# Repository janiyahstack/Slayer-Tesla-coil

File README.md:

# Slayer-Tesla-coil
A slayer Excited Tesla coil is a low power solid state tesla coil. A tesla coil is a high frequency transformer that is used to generate high voltages of electricity. It is self-oscillating and does not require precise tuning. A tesla coil was first created by Nikola Tesla in 1891, at the time it was a transformative step in his dream of acquiring wireless transmission of electricity, while we continue to use wire to transmit energy till date, it makes for an exciting project.
I was most inspired to make a Tesla coil by one of my fellow hack clubbers (whose name i cant remember), who made me realize that a tesla coil was quite achievable to make and design. i have been interested in it for a while and it was fun to do.
I built this by first understanding the physics behind a Tesla coil; electromagnetic induction. Then i made a schematic, i read more which led to consequential iterations of the schematic. I did the footprints assignments using Mouser Electronics and eventually updated my footprint library. i concluded by making the PCB(some of the parts are external tho) and viola!!

STEP 1
I did research on Tesla coils. Theres a lot of info about spark gap tesla coils but i decided to go with a slayer excited tesla coil instead utilizing either a feedback coil or a transistor. More details canbe found in the journal.md. Anyways after deciding on this. I read a bunch of instructions and watched YouTube videos and then made the schematic.

STEP 2
I got carried away although doing the footprints assignment but i do think it helped a lot in making the BOM and i made a PCB cause i thought it will be useful which it could be but my tesla coil is not using a PCB

step 3
I made the CAD which also helped me narrow down the specifications etcetra, get a better idea of what i am trying to do and gave me resources to use o calculate the resonant frequency which is important but not too much in a slayer excited tesla coil

step 4
I made the BOM, i looked through Ali Express for stuff, i decided on a battery which i hope i did well cause i dont want to use an adapter and voila. More details in Journal.md

The BOM
pandoc -f csv Sheet1.csv -o output.md

https://docs.google.com/spreadsheets/d/1osx8s_dKkFnwftt5uLbFzMi76YqxEO74YxG5Nzp4THI/edit?usp=sharing

The Schematic

The CAD

| Reference | QTY | Component | Value | Notes | Estimated Prices | Link |
|---|---:|---|---|---|---:|---|
| Q2 | 1 | NPN Power Transistor | TIP31C | TO-220 Package | $1.10 per 10pcs | https://a.aliexpress.com/_EGoSctg |
| R2 | 1 | Resistor | 1kohms | Axial | Available | Available |
| C1 | 1 | Ceramic Capacitor | 100nF, 50V | Radial | $1.10 per 10pcs | https://a.aliexpress.com/_ExHqb2e |
| D2 | 1 | Diode | BAV16W | Fast switching | $0.86 for 20pcs | https://a.aliexpress.com/_EG9ENKm |
| L1 | 1 | Primary coil | 4 turns, 0.8mm magnet wire | Custom wound | $2.80 | https://a.aliexpress.com/_EzIT5KI |
| L2 | 1 | Secondary coil | 25 turns, 0.2mm magnet wire | Custom wound | $1.10 | https://a.aliexpress.com/_EIRpH5y |
| L3 | 1 | Feedback coil | 3 turns, 0.6mm magnet wire | Custom wound | $1.10 | https://a.aliexpress.com/_EIRpH5y |
| BT1 | 1 | Power supply | 9V Lithium ion battery | | $1.10 | https://a.aliexpress.com/_EwdnAp0 |
| 2 pin screw terminal | 2 | 2-pin screw terminal | 2-pin screw terminal | Power input | $1.23 | https://a.aliexpress.com/_Eze3ZSI |
| Perf Board | 1 | Perfboard | 7×9cm protoboard | Circuit Assembly | $1.10 | https://a.aliexpress.com/_EyrP0P4 |
| Solder iron | 1 | Solder Iron | USB or mains powered | Required tool | $6.96 | https://a.aliexpress.com/_EwgpuvC |
| PVC pipe | 1 | PVC pipe | 4 inches | Coil former | $1.10 for 2 pcs | https://a.aliexpress.com/_EzJuh94 |
| | | | | **Total** | **$19.55** | |

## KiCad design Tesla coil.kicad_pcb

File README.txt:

# Slayer-Tesla-coil
A slayer Excited Tesla coil is a low power solid state tesla coil. A tesla coil is a high frequency transformer that is used to generate high voltages of electricity. It is self-oscillating and does not require precise tuning. A tesla coil was first created by Nikola Tesla in 1891, at the time it was a transformative step in his dream of acquiring wireless transmission of electricity, while we continue to use wire to transmit energy till date, it makes for an exciting project.
I was most inspired to make a Tesla coil by one of my fellow hack clubbers (whose name i cant remember), who made me realize that a tesla coil was quite achievable to make and design. i have been interested in it for a while and it was fun to do.
I built this by first understanding the physics behind a Tesla coil; electromagnetic induction. Then i made a schematic , i read more which led to consequential iterations of the schematic. I did the footprints assignments using Mouser Electronics and eventually updated my footprint library. i concluded by making the PCB(some of the parts are external tho) and viola!!
.png)
.png).

STEP 1
I did research on Tesla coils. Theres a lot of info about spark gap tesla coils but i decided to go with a slayer excited tesla coil instead utilizing either a feedback coil or a transistor. More details canbe found in the journal.md

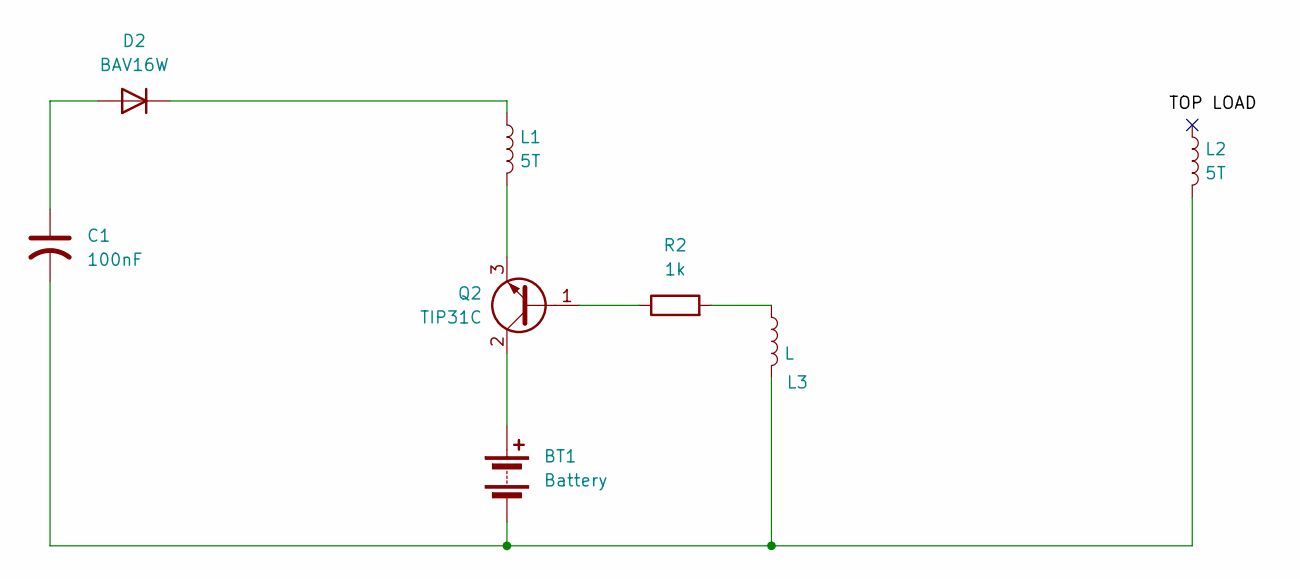
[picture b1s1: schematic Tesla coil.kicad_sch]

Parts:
BT1: Battery; TerminalBlock_MaiXu_MX126-5.0-02P_1x02_P5.00mm
C1: 100nF; CP_Axial_L11.0mm_D6.0mm_P18.00mm_Horizontal
D2: BAV16W; D_SOD-123
L1, L2: 5T; TerminalBlock_MaiXu_MX126-5.0-02P_1x02_P5.00mm
L3: L; TerminalBlock_MaiXu_MX126-5.0-02P_1x02_P5.00mm
Q2: TIP31C; TO-220-3
R2: 1k; R_Axial_DIN0414_L11.9mm_D4.5mm_P5.08mm_Vertical

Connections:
unnamed: BT1.1 (+), Q2.2 (C)
unnamed: BT1.2 (-), C1.2, L2.2, L3.2
unnamed: C1.1, D2.2 (A)
unnamed: D2.1 (K), L1.1
unnamed: L3.1, R2.2
unnamed: Q2.1 (B), R2.1
unnamed: L1.2, Q2.3 (E)

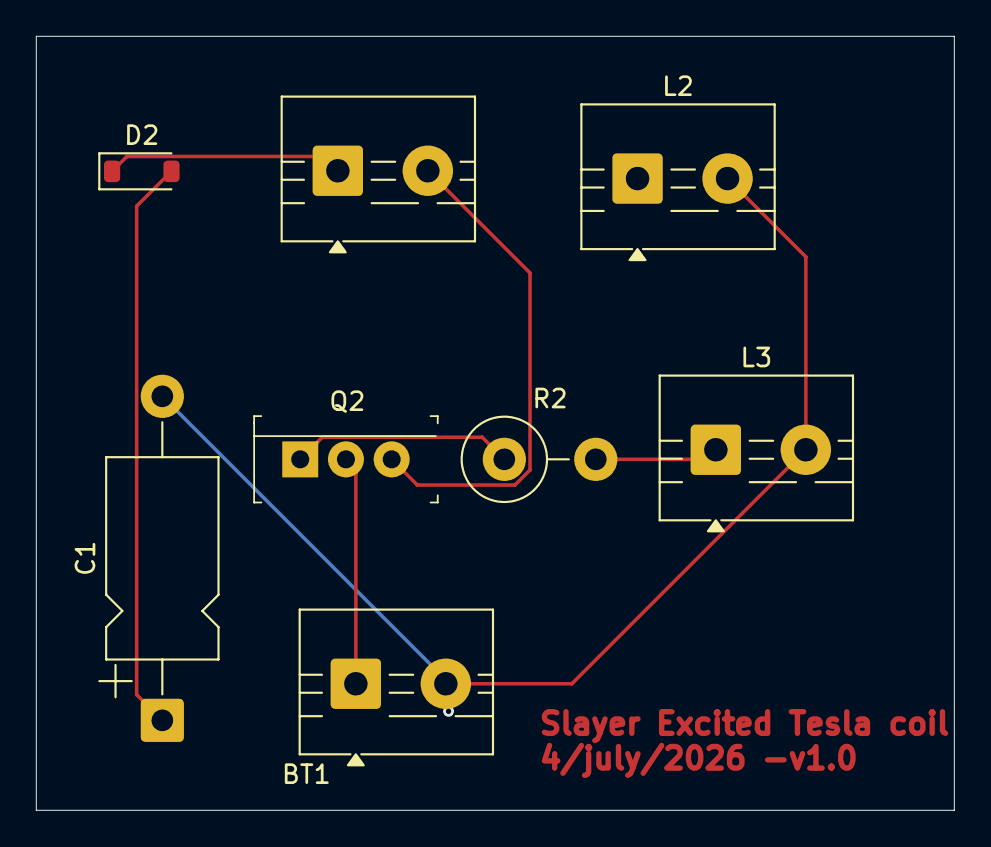
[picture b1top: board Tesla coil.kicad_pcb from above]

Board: 4 copper layers, 51.0 x 43.0 mm, 8 parts (0 on the bottom side), 7 nets.

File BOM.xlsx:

Reference | QTY | Component | Value/Part Number | Notes
Q2 | 1 | NPN Power Transistor | TIP31C | TO-220 Package
R2 | 1 | Resistor | 1kohms, 1/4 W | Axial
C1 | 1 | Ceramic Capacitor | 100nF, 50v | Radial
D2 | 1 | Diode | BAV16W | Fast switching
L1 | 1 | Primary Coil | 5 turns, 0.8mm magnet wire | Custom wound
L2 | 1 | Secondary Coil | 400 turns, 0.2mm magnet wire | Custom wound
L3 | 1 | Feedback Coil | 5 turns, 0.6mm magnet wire | Custom wound
BT1 | 1 | Power supply | 12V DC | Battery or DC Adapter
